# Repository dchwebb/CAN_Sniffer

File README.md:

# CAN_Sniffer

CAN Bus sniffer developed for STM32F429 platform using the STM32F429 Discovery board. This connects to a car's dashboard CAN bus via a NXP TJA1050 transceiver over the OBD2 protocol.

The OBD2 protocol is an industry-wide standard to provide access to a vehicle's self-diagnostic data via the CAN bus. The CAN Sniffer provides a GUI displaying real-time statistics decoded from the OBD2 protocol.

CAN Sniffer has been tested with a Ford Mondeo and Audi A3.

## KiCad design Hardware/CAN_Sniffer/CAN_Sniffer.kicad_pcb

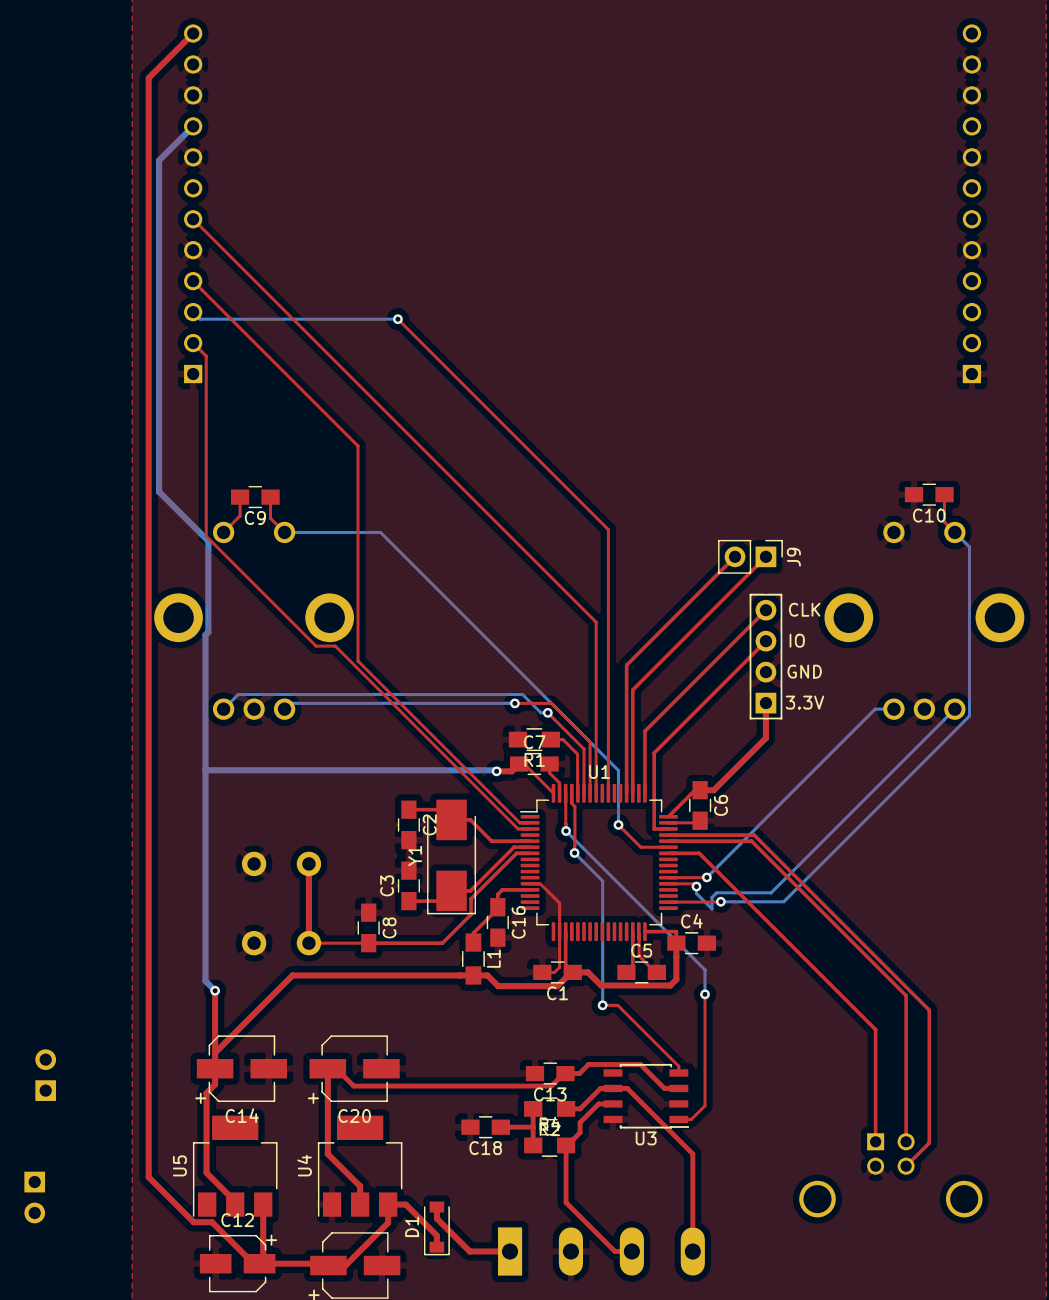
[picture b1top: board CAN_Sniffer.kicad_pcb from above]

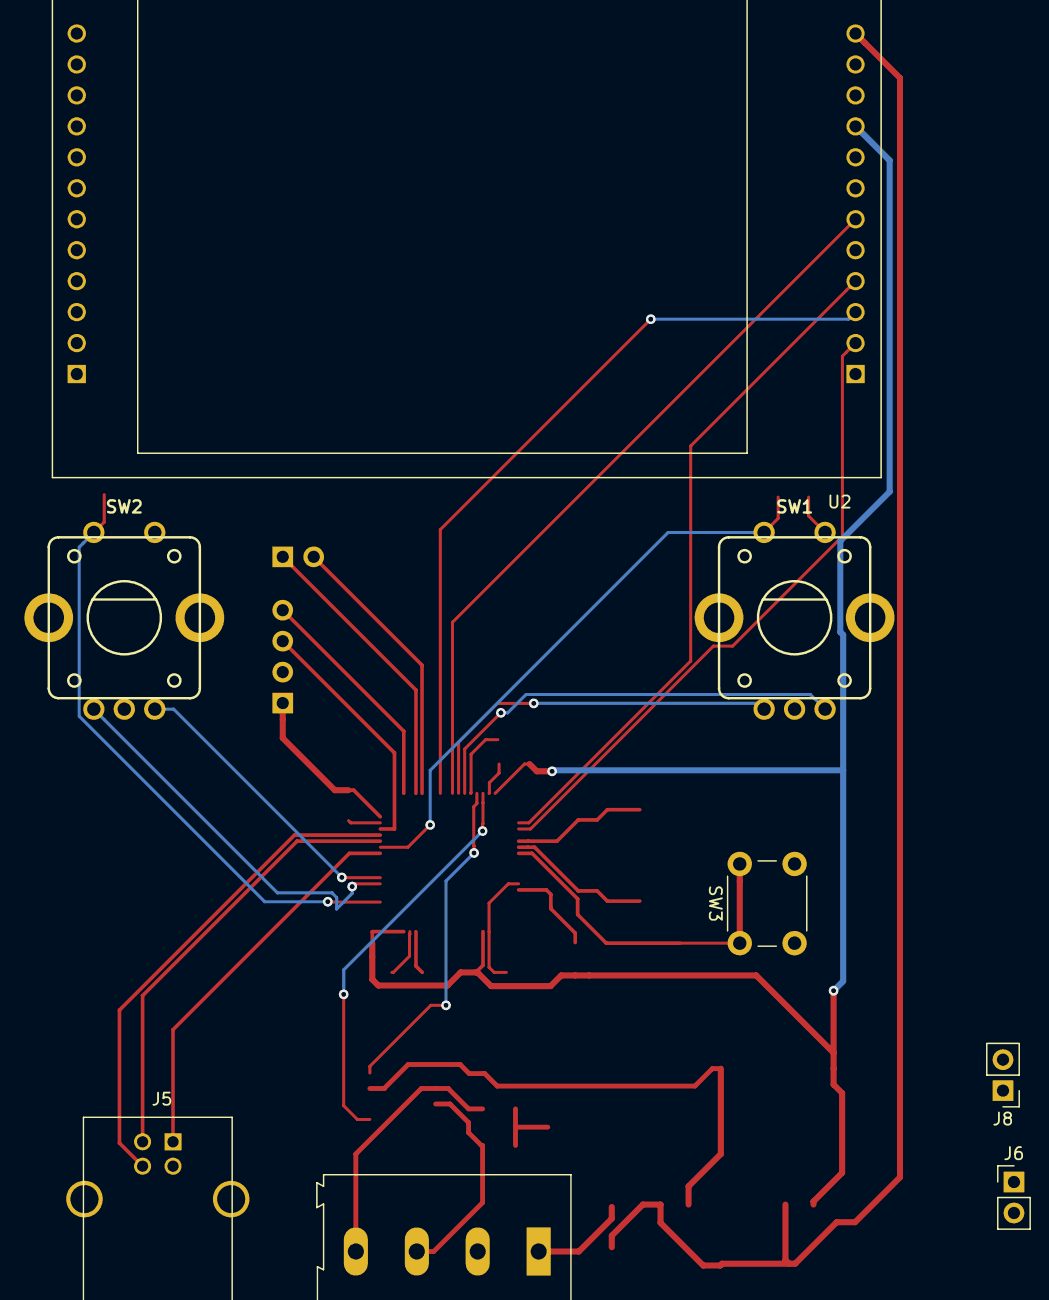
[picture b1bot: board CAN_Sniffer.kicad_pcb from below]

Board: 2 copper layers, 37 parts (8 on the bottom side), 34 nets.

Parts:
C1, C4, C6, C7, C8, C9, C10, C13, C16: 100nF; C_0805_HandSoldering
C2, C3: 18pF; C_0805_HandSoldering
C5: 2.2uF; C_0805_HandSoldering
C12: 22uF; CP_Elec_4x5.8
C14: 47uF; CP_Elec_5x5.8
C18: 47nF; C_0805_HandSoldering
C19: 10uF; CP_Elec_5x5.8
C20: 22uF; CP_Elec_5x5.8
D1: 1N5819; D_SOD-123
J1: SWD_Header; SWD_header
J5: USB_B_Micro; USB_B_Molex
J6, J8, J9: Conn_01x02; Socket_Strip_Straight_1x02_Pitch2.54mm
J7: CAN Header; TerminalBlock_Altech_AK300-4_P5.00mm
L1: L; R_0805_HandSoldering
R1: 10k; R_0805_HandSoldering
R2, R4: 60; R_0805_HandSoldering
SW1: Left_Encoder; Encoder
SW2: Right_Encoder; Encoder
SW3: SW_Push; SW_PUSH_6mm
U1: STM32F446RETx; LQFP-64_10x10mm_P0.5mm
U2: ILI9341_SPI_Daughterboard; ILI9341_SPI_daughterboard
U3: TJA1051T; SOIC-8_3.9x4.9mm_Pitch1.27mm
U4: LM1117-5.0; SOT-223
U5: LM1117-3.3; SOT-223
Y1: Crystal; Crystal_SMD_0603-2pin_6.0x3.5mm_HandSoldering

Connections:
+3.3VA: C16.1, L1.1, U1.13
+3V3: C1.1, C4.1, C6.1, C7.1, C14.1, J1.1, J8.1, L1.2, U1.19, U1.32, U1.48, U1.64, U2.9, U5.2
+5V: C13.1, C20.1, J6.1, U3.3, U4.2
+12V: D1.2, J7.1
CAN1_RX: U1.61, U3.4
CAN1_TX: U1.62, U3.1
CANH: J7.3, R4.2, U3.7
CANL: J7.4, R2.1, U3.6
GND: C1.2, C2.2, C3.2, C4.2, C5.2, C6.2, C7.2, C8.1, C10.2, C12.2, C13.2, C14.2, C16.2, C18.2, C19.2, C20.2, J1.2, J5.4, J6.2, J7.2, J8.2, R1.2, SW1.C, SW2.C, SW2.S2, SW3.2, U1.12, U1.18, U1.31, U1.47, U1.63, U2.1, U2.5, U2.8, U2.10, U2.11, U2.13, U2.17, U2.20, U2.22, U2.23, U3.2, U3.8, U4.1, U5.1
LCD_DC: U1.2, U2.4
LCD_MOSI: U1.57, U2.6
LCD_RESET: U1.3, U2.2
LCD_SCK: U1.55, U2.3
L_ENC_BTN: C9.1, SW1.S1, U1.43
L_ENC_DN: SW1.B, U1.59
L_ENC_UP: SW1.A, U1.58
NRST: C8.2, SW3.1, U1.7
unnamed: C2.1, U1.5, Y1.2
unnamed: C3.1, U1.6, Y1.1
unnamed: C5.1, U1.30
unnamed: C9.2, SW1.S2
unnamed: C18.1, R2.2, R4.1
unnamed: R1.1, U1.60
R_ENC_BTN: C10.1, SW2.S1, U1.34
R_ENC_DN: SW2.B, U1.38
R_ENC_UP: SW2.A, U1.37
SWCLK: J1.4, U1.49
SWDIO: J1.3, U1.46
USART3_RX: J9.2, U1.52
USART3_TX: J9.1, U1.51
USB_DM: J5.2, U1.44
USB_DP: J5.3, U1.45
USB_VBUS: J5.1, U1.42
VCC: C12.1, C19.1, D1.1, U2.12, U4.3, U5.3

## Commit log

2020-05-02 Started coding CAN Bus initialisation and transmit
2020-05-03 CAN Bus transmission working
2020-05-04 CAN Sending and receiving working via loopback with lcd display
2020-05-04 Added CAN handler class; filtering on multiple IDs working
2020-05-04 Further tests of filtering
2020-05-05 Minor cleanups to CAN filtering
2020-05-06 Added USART mode to control display through virtual COM port
    Also updated UI to allow paging of captured CAN events
2020-05-06 Added CAN detail UI
2020-05-06 Added updated time to ID display mode
2020-05-07 Tested working sniffing car traffic
    - Added command to activate test mode to send dummy data
    - Added command to dump captured data to serial port
    - display count of captured items on list screen
    - Store number of hits of each ID captured
2020-05-09 Cleaned up some text handling functions
2020-05-09 Clean up of CAN class; events now held in vector (previously deque)
2020-05-11 Implemented OBD2 query mode; started implementing full diagnostic info mode
2020-05-11 Completed available PID query logic
2020-05-11 First draft of OBD2 info display
2020-05-12 SAE Info mode working
2020-05-12 Added genuine CAN pcakets as dummy data for offline testing
2020-05-12 More work on diagnostic info
2020-05-13 Reworked a number of display options and started support for service 9 diagnostics
2020-05-15 Fixed page bug
2020-05-16 Extensive refactoring to support multi-fraem messages (not yet working)
2020-05-18 Refactoring and further support for multi-frame packets
    Also started schematic
2020-05-18 Multi-frame packet logic largely working
2020-05-18 Multi frame data tested and working
2020-05-19 First draft of PCB layout
2020-05-20 Code cleanup
2020-05-20 Code refactoring and cleaning
2020-05-21 Prepared trouble-shooting backups
2020-05-22 Updates for Audi diagnostics
2020-05-22 Introduced inheritance for OBD items; added basic decoding for remaining Audi codes
2021-09-23 Formatting
